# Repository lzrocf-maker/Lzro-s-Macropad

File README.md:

# Lzro's_Macropad

This is a custom-built macropad for various usecases. The goal is to have different macros for different apps so that when you change app the macros change. It also has a ring with SK6812Mini LEDs. It has 10 mx cherry switches for the macro buttons. Here is a photo of how the macropad is suposed to look like when assembled:

## Project Overview
I have built this macropad so that every switch is directly connected to one GPIO pin on the XIAO RP2040. A feature that will be added some time in the near future is LED reactivity, so that when you click a button, the LEDs make a wave from were the button is located.

## Hardware Specifications
- **Microcontroller:** Seeed Studio XIAO RP2040.
- **Switches:** 10x MX mechanical switches.
- **Lighting:** 16x addressable RGB LEDs (SK6812 Mini) in three stripes (all connected to one GPIO pin).
- **Mounting:** M3 hardware with heat-set inserts with a 3d printed case printed in to halves.

## Pinout Reference
These are the pinouts of the XIAO board to all the components:

| Component | XIAO Pin | GPIO |
| :--- | :--- | :--- |
| **Switches 1-4** | D26, D27, D28, D29 | GPIO26, 27, 28, 29 |
| **Switches 5-6** | D6, D7 | GPIO6, 7 |
| **Switches 7-10**| D0, D1, D2, D3 | GPIO0, 1, 2, 3 |
| **RGB Data** | D4 | GPIO4 |

## 3D Enclosure & Assembly
I designed the case so that you only have to print 2 parts, the two halves come together with 4 M3 screws and heat-set inserts:

- **Top Plate:** I designed the top part with the cutouts for the 10 switches as well as a cutout to see the controller and a bit of the PCB, I also added 3 0.20mm thick stripes as diffusers for the LED lights (wich can be printed in white while the rest of the body is printed in black. If you don't have a multicolor 3d printer you can print the entire to part in white, although there will be light bleed.
  
- **Bottom Base:** The bottom part features a recesed part so that the pins of the switches do not crash onto the case. It also has 4 countersunc holes for the 4 M3 screws. Some anti-slip pads can be added beside the holes for better grip on the desk, although it is not needed for it to function.

## Firmware
This project runs **KMK** on **CircuitPython**.

## Repository Contents
- The files ended on .kicad_sch/pro/pcb are the PCB files.
- The Gerbers.zip contains the files for PCB manufacturing.
- The files with the name screenshot contain photos of the product.
- The file code.py contains the core firmware for the pcb to work (it can be changed to your specific needs).
- Lzro's_Macropad.step contains the 3d model of the macropad.
- The BOM file contains all the list of materials needed for manufacturing this project.

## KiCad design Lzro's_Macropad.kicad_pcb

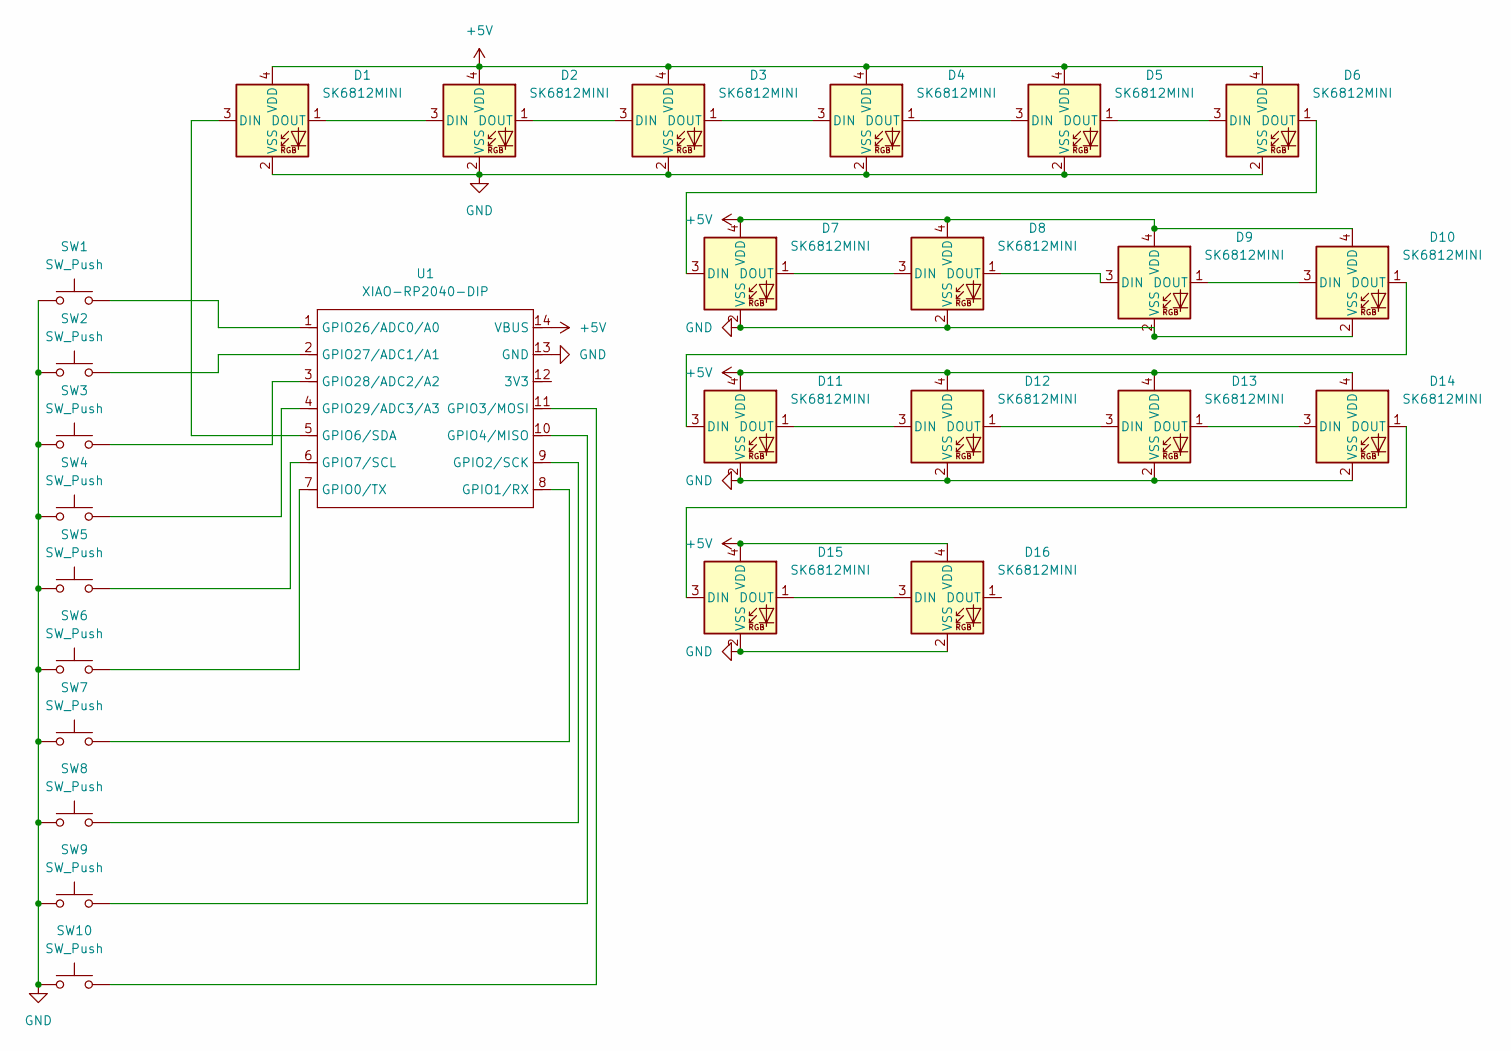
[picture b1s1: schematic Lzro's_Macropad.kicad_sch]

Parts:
D1, D2, D3, D4, D5, D6, D7, D8, D9, D10, D11, D12, D13, D14, D15, D16: SK6812MINI; LED_SK6812MINI_PLCC4_3.5x3.5mm_P1.75mm
SW1, SW2, SW3, SW4, SW5, SW6, SW7, SW8, SW9, SW10: SW_Push; SW_Cherry_MX_1.00u_PCB
U1: XIAO-RP2040-DIP

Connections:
+5V: D1.4 (VDD), D2.4 (VDD), D3.4 (VDD), D4.4 (VDD), D5.4 (VDD), D6.4 (VDD), D7.4 (VDD), D8.4 (VDD), D9.4 (VDD), D10.4 (VDD), D11.4 (VDD), D12.4 (VDD), D13.4 (VDD), D14.4 (VDD), D15.4 (VDD), D16.4 (VDD), U1.14 (VBUS)
GND: D1.2 (VSS), D2.2 (VSS), D3.2 (VSS), D4.2 (VSS), D5.2 (VSS), D6.2 (VSS), D7.2 (VSS), D8.2 (VSS), D9.2 (VSS), D10.2 (VSS), D11.2 (VSS), D12.2 (VSS), D13.2 (VSS), D14.2 (VSS), D15.2 (VSS), D16.2 (VSS), SW1.1, SW2.1, SW3.1, SW4.1, SW5.1, SW6.1, SW7.1, SW8.1, SW9.1, SW10.1, U1.13 (GND)
unnamed: D1.3 (DIN), U1.5 (GPIO6/SDA)
unnamed: D1.1 (DOUT), D2.3 (DIN)
unnamed: D2.1 (DOUT), D3.3 (DIN)
unnamed: D3.1 (DOUT), D4.3 (DIN)
unnamed: D4.1 (DOUT), D5.3 (DIN)
unnamed: D5.1 (DOUT), D6.3 (DIN)
unnamed: D6.1 (DOUT), D7.3 (DIN)
unnamed: D7.1 (DOUT), D8.3 (DIN)
unnamed: D8.1 (DOUT), D9.3 (DIN)
unnamed: D9.1 (DOUT), D10.3 (DIN)
unnamed: D10.1 (DOUT), D11.3 (DIN)
unnamed: D11.1 (DOUT), D12.3 (DIN)
unnamed: D12.1 (DOUT), D13.3 (DIN)
unnamed: D13.1 (DOUT), D14.3 (DIN)
unnamed: D14.1 (DOUT), D15.3 (DIN)
unnamed: D15.1 (DOUT), D16.3 (DIN)
unnamed: SW6.2, U1.7 (GPIO0/TX)
unnamed: SW7.2, U1.8 (GPIO1/RX)
unnamed: SW8.2, U1.9 (GPIO2/SCK)
unnamed: SW10.2, U1.11 (GPIO3/MOSI)
unnamed: SW9.2, U1.10 (GPIO4/MISO)
unnamed: SW5.2, U1.6 (GPIO7/SCL)
unnamed: SW1.2, U1.1 (GPIO26/ADC0/A0)
unnamed: SW2.2, U1.2 (GPIO27/ADC1/A1)
unnamed: SW3.2, U1.3 (GPIO28/ADC2/A2)
unnamed: SW4.2, U1.4 (GPIO29/ADC3/A3)

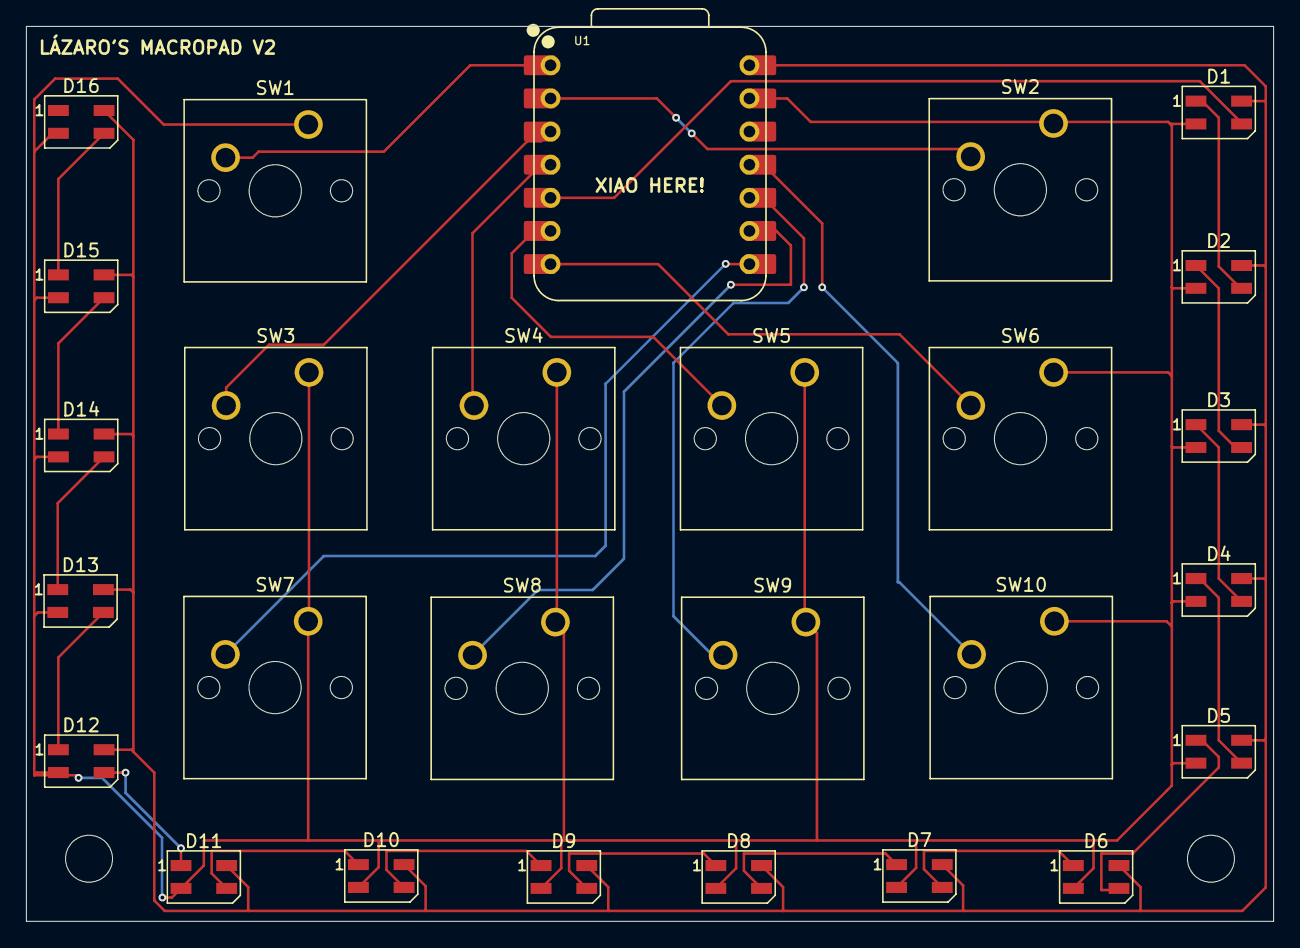
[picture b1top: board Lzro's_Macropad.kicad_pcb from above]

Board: 2 copper layers, 95.6 x 68.6 mm, 27 parts (0 on the bottom side), 28 nets.

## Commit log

2026-01-12 Rename BOM Lzro's Trackpad.pdf to BOM Lzro's Macropad.pdf
2026-01-13 Create hardware
2026-01-13 Update and rename hardware to
